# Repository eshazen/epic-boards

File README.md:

# epic-boards
Various small projects for EPIC and ENG classes

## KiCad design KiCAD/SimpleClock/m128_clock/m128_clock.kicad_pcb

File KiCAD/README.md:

Various small PCB projects for EPIC

    JumperBoards     - jumper boards for machine wiring
	me310-diff-amp   - instrumentation amp for ME310 class

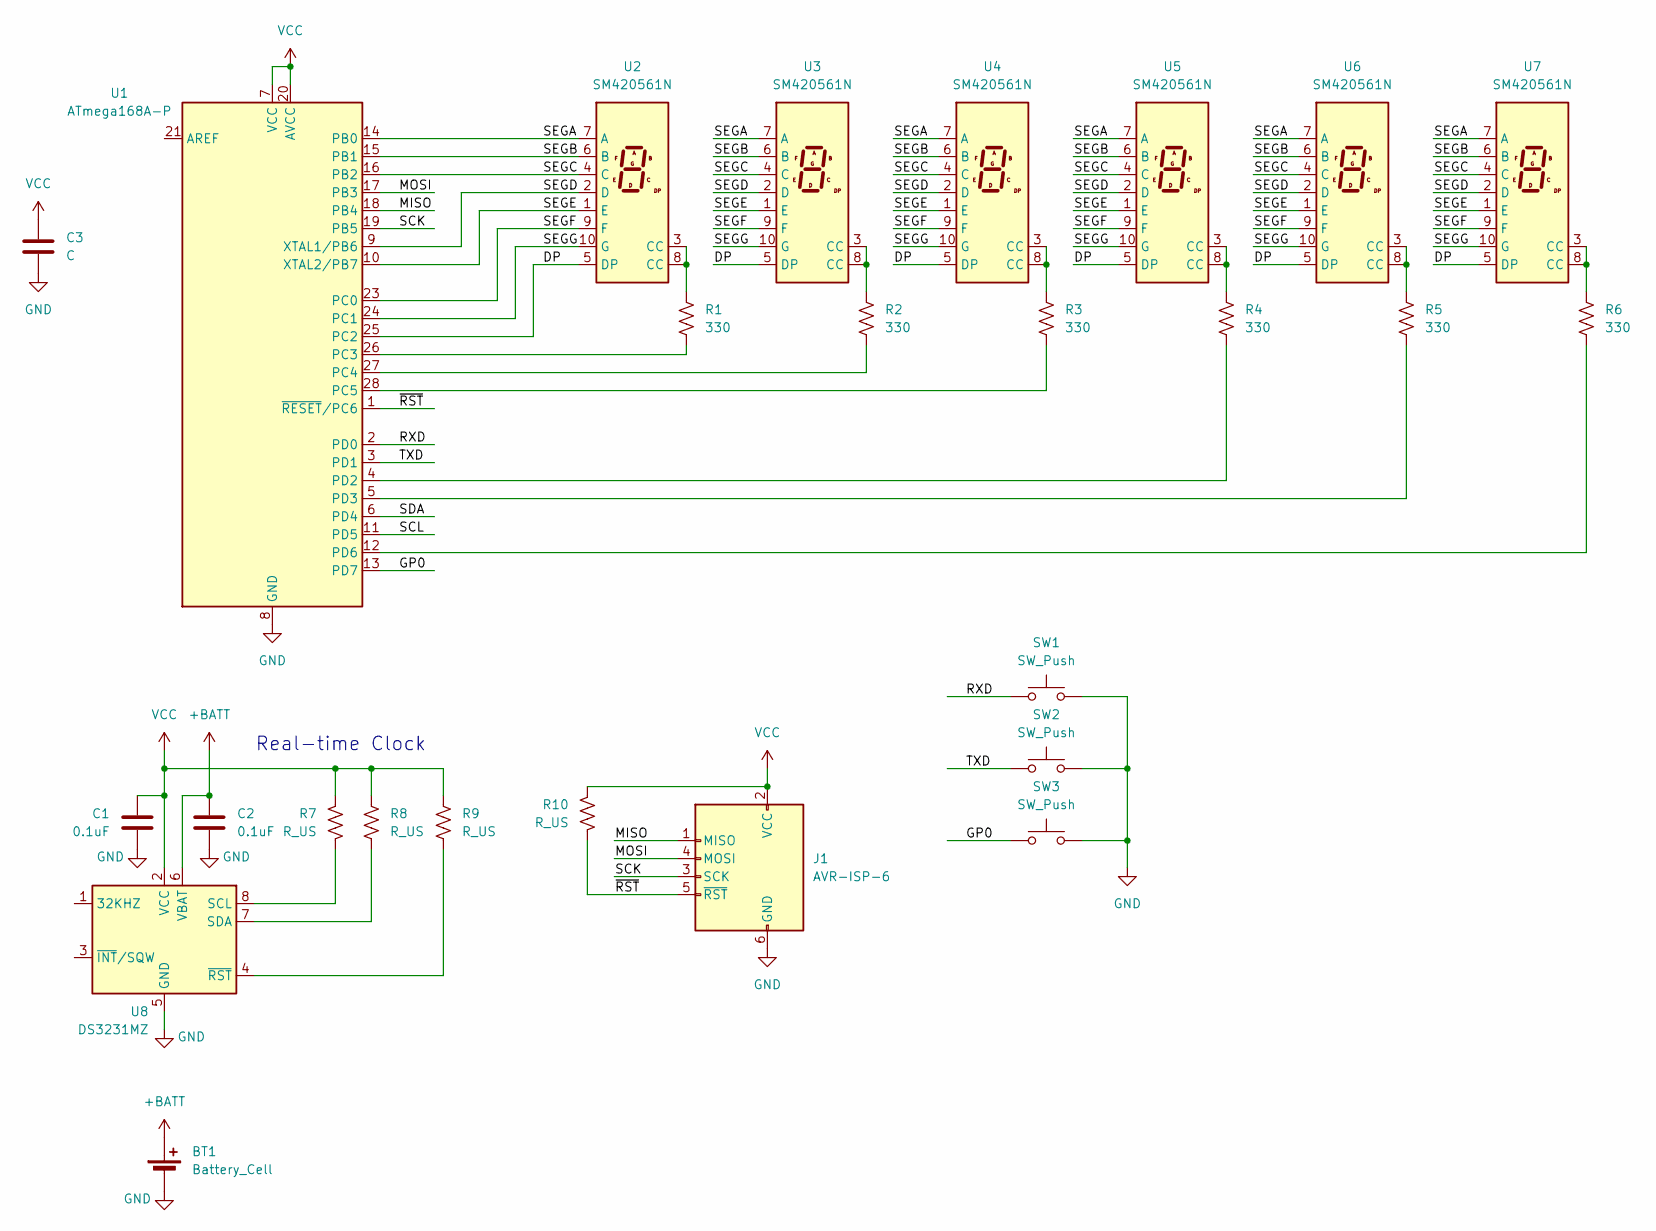
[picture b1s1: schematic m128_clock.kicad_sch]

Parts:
BT1: Battery_Cell; BatteryHolder_Keystone_103_1x20mm
C1, C2: 0.1uF; C_1206_3216Metric_Pad1.33x1.80mm_HandSolder
C3: C; C_Disc_D7.0mm_W2.5mm_P5.00mm
J1: AVR-ISP-6; PinHeader_2x03_P2.54mm_Vertical
R1, R2, R3, R4, R5, R6: 330; R_Axial_DIN0309_L9.0mm_D3.2mm_P12.70mm_Horizontal
R7, R8, R9, R10: R_US; R_1206_3216Metric
SW1, SW2, SW3: SW_Push; Push_SW
U1: ATmega168A-P; DIP-28_W7.62mm
U2, U3, U4, U5, U6, U7: SM420561N; 7SegmentLED_LTS6760_LTS6780
U8: DS3231MZ; SOIC-8_3.9x4.9mm_P1.27mm

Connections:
+BATT: BT1.1 (+), C2.1, U8.6 (VBAT)
/DP: U1.25 (PC2), U2.5 (DP), U3.5 (DP), U4.5 (DP), U5.5 (DP), U6.5 (DP), U7.5 (DP)
/GP0: SW3.1, U1.13 (PD7)
/MISO: J1.1 (MISO), U1.18 (PB4)
/MOSI: J1.4 (MOSI), U1.17 (PB3)
/RXD: SW1.1, U1.2 (PD0)
/SCK: J1.3 (SCK), U1.19 (PB5)
/SCL: U1.11 (PD5)
/SDA: U1.6 (PD4)
/SEGA: U1.14 (PB0), U2.7 (A), U3.7 (A), U4.7 (A), U5.7 (A), U6.7 (A), U7.7 (A)
/SEGB: U1.15 (PB1), U2.6 (B), U3.6 (B), U4.6 (B), U5.6 (B), U6.6 (B), U7.6 (B)
/SEGC: U1.16 (PB2), U2.4 (C), U3.4 (C), U4.4 (C), U5.4 (C), U6.4 (C), U7.4 (C)
/SEGD: U1.9 (XTAL1/PB6), U2.2 (D), U3.2 (D), U4.2 (D), U5.2 (D), U6.2 (D), U7.2 (D)
/SEGE: U1.10 (XTAL2/PB7), U2.1 (E), U3.1 (E), U4.1 (E), U5.1 (E), U6.1 (E), U7.1 (E)
/SEGF: U1.23 (PC0), U2.9 (F), U3.9 (F), U4.9 (F), U5.9 (F), U6.9 (F), U7.9 (F)
/SEGG: U1.24 (PC1), U2.10 (G), U3.10 (G), U4.10 (G), U5.10 (G), U6.10 (G), U7.10 (G)
/TXD: SW2.1, U1.3 (PD1)
/~RST: J1.5 (~RST), R10.2, U1.1 (~RESET/PC6)
GND: BT1.2 (-), C1.2, C2.2, C3.2, J1.6 (GND), SW1.2, SW2.2, SW3.2, U1.8 (GND), U1.22 (GND), U8.5 (GND)
unnamed: R1.1, U2.3 (CC), U2.8 (CC)
unnamed: R2.1, U3.3 (CC), U3.8 (CC)
unnamed: R3.1, U4.3 (CC), U4.8 (CC)
unnamed: R4.1, U5.3 (CC), U5.8 (CC)
unnamed: R5.1, U6.3 (CC), U6.8 (CC)
unnamed: R6.1, U7.3 (CC), U7.8 (CC)
unnamed: R1.2, U1.26 (PC3)
unnamed: R2.2, U1.27 (PC4)
unnamed: R3.2, U1.28 (PC5)
unnamed: R4.2, U1.4 (PD2)
unnamed: R5.2, U1.5 (PD3)
unnamed: R6.2, U1.12 (PD6)
unnamed: R7.2, U8.8 (SCL)
unnamed: R8.2, U8.7 (SDA)
unnamed: R9.2, U8.4 (~RST)
VCC: C1.1, C3.1, J1.2 (VCC), R7.1, R8.1, R9.1, R10.1, U1.7 (VCC), U1.20 (AVCC), U8.2 (VCC)

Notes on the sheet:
Real-time Clock

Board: 2 copper layers, 26 parts (0 on the bottom side), 33 nets, no tracks yet.

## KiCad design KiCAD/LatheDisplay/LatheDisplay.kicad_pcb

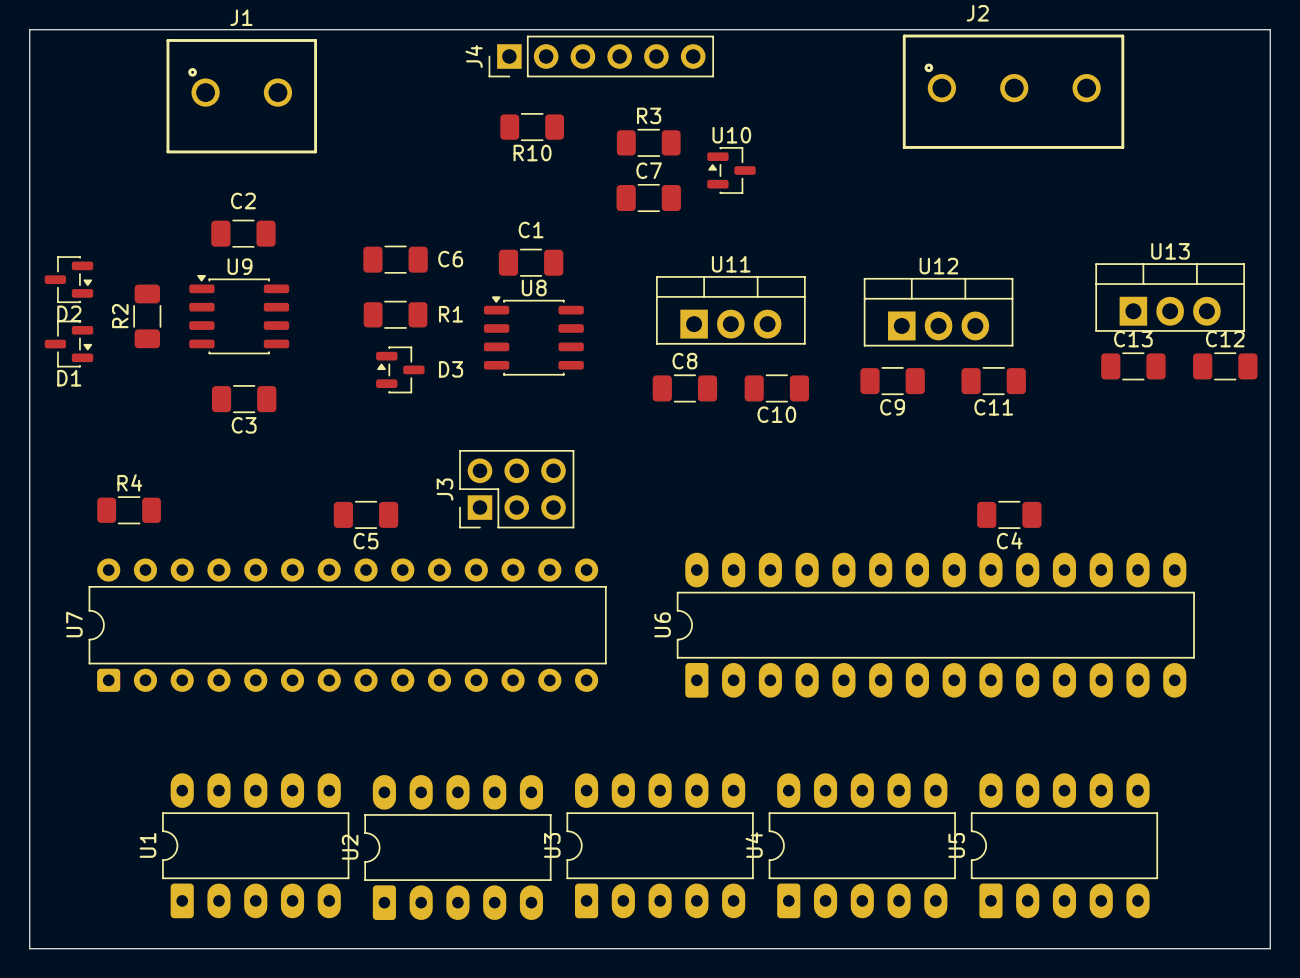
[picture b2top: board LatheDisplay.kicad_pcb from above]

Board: 2 copper layers, 85.7 x 63.5 mm, 38 parts (0 on the bottom side), 45 nets, no tracks yet.

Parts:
C1, C2, C3, C4, C5, C6, C7, C8, C9, C10, C11, C12, C13: 0.1uF; C_1206_3216Metric_Pad1.33x1.80mm_HandSolder
D1, D2, D3: BAV99; SOT-23
J1: Screw_Terminal_01x02; 691137710002
J2: Screw_Terminal_01x03; 3-pin-terminal
J3: AVR-ISP-6; PinHeader_2x03_P2.54mm_Vertical
J4: Conn_01x06_Pin; PinHeader_1x06_P2.54mm_Vertical
R1, R3, R4: 2k; R_1206_3216Metric_Pad1.30x1.75mm_HandSolder
R2: RGAIN; R_1206_3216Metric_Pad1.30x1.75mm_HandSolder
R10: 0R; R_1206_3216Metric_Pad1.30x1.75mm_HandSolder
U1, U2, U3, U4, U5: D168K; DIP-10_W7.62mm_LongPads
U6: ICM7218B; DIP-28_W7.62mm_LongPads
U7: ATmega328-P; DIP-28_W7.62mm
U8: TLC3541; SO-8_3.9x4.9mm_P1.27mm
U9: INA121; SO-8_3.9x4.9mm_P1.27mm
U10: LM4040DBZ-4.1; SOT-23
U11: LM7812_TO220; TO-220-3_Vertical
U12: LM7912_TO220; TO-220-3_Vertical
U13: LM7805_TO220; TO-220-3_Vertical

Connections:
+5V: C1.1, C4.1, C5.1, C12.1, D3.2 (A), J3.2 (VCC), R4.2, R10.1, U6.19 (V+), U7.7 (VCC), U7.20 (AVCC), U8.6 (VDD), U13.3 (VO)
+12V: C2.1, C10.1, D1.2 (A), D2.2 (A), R3.2, U9.8 (V+), U11.3 (VO)
+15V: C8.1, C13.1, J2.1, U11.1 (VI), U13.1 (VI)
-12V: C3.1, C11.1, D1.1 (K), D2.1 (K), U9.5 (V-), U12.3 (VO)
-15V: C9.1, J2.3, U12.2 (VI)
/ADC_CS: U7.6 (PD4), U8.1 (~CS)
/DP: U1.5 (DP), U2.5 (DP), U3.5 (DP), U4.5 (DP), U5.5 (DP), U6.4 (dp)
/FS: U7.5 (PD3), U8.7 (FS)
/MISO: J3.1 (MISO), U7.18 (PB4), U8.8 (SDO)
/MOSI: J3.4 (MOSI), U7.17 (PB3)
/RXD: J4.4, U7.2 (PD0)
/SA: U1.7 (A), U2.7 (A), U3.7 (A), U4.7 (A), U5.7 (A), U6.27 (a)
/SB: U1.6 (B), U2.6 (B), U3.6 (B), U4.6 (B), U5.6 (B), U6.3 (b)
/SC: U1.4 (C), U2.4 (C), U3.4 (C), U4.4 (C), U5.4 (C), U6.1 (c)
/SCK: J3.3 (SCK), U7.19 (PB5), U8.5 (SCLK)
/SD: U1.2 (D), U2.2 (D), U3.2 (D), U4.2 (D), U5.2 (D), U6.25 (d)
/SE: U1.1 (E), U2.1 (E), U3.1 (E), U4.1 (E), U5.1 (E), U6.2 (e)
/SF: U1.9 (F), U2.9 (F), U3.9 (F), U4.9 (F), U5.9 (F), U6.24 (f)
/SG: U1.10 (G), U2.10 (G), U3.10 (G), U4.10 (G), U5.10 (G), U6.26 (g)
/TXD: J4.5, U7.3 (PD1)
/~RESET: J3.5 (~RST), R4.1, U7.1 (~RESET/PC6)
GND: C1.2, C2.2, C3.2, C4.2, C5.2, C6.2, C7.2, C8.2, C9.2, C10.2, C11.2, C12.2, C13.2, D3.1 (K), J2.2, J3.6 (GND), J4.1, U6.28 (GND), U7.8 (GND), U7.22 (GND), U8.3 (GND), U9.6 (Ref), U10.2 (A), U11.2 (GND), U12.1 (GND), U13.2 (GND)
unnamed: D1.3 (K), J1.1, U9.4 (+)
unnamed: D2.3 (K), J1.2, U9.1 (-)
unnamed: J4.3, R10.2
unnamed: R1.1, U9.7
unnamed: R2.1, U9.3 (Rg)
unnamed: R2.2, U9.2 (Rg)
unnamed: U6.12 (ID0), U7.14 (PB0)
unnamed: U6.11 (ID1), U7.15 (PB1)
unnamed: U6.13 (ID2), U7.16 (PB2)
unnamed: U6.14 (ID3), U7.9 (XTAL1/PB6)
unnamed: U6.10 (ID4), U7.10 (XTAL2/PB7)
unnamed: U6.6 (ID5), U7.23 (PC0)
unnamed: U6.5 (ID6), U7.24 (PC1)
unnamed: U6.7 (ID7), U7.25 (PC2)
unnamed: U6.9 (MODE), U7.4 (PD2)
unnamed: U1.3 (CC), U1.8 (CC), U6.15 (d1)
unnamed: U2.3 (CC), U2.8 (CC), U6.16 (d2)
unnamed: U3.3 (CC), U3.8 (CC), U6.23 (d3)
unnamed: U4.3 (CC), U4.8 (CC), U6.20 (d4)
unnamed: U5.3 (CC), U5.8 (CC), U6.17 (d5)
unnamed: U6.8 (nWR), U7.26 (PC3)
unnamed: C6.1, D3.3 (K), R1.2, U8.4 (AIN)
unnamed: C7.1, R3.1, U8.2 (REF), U10.1 (K)

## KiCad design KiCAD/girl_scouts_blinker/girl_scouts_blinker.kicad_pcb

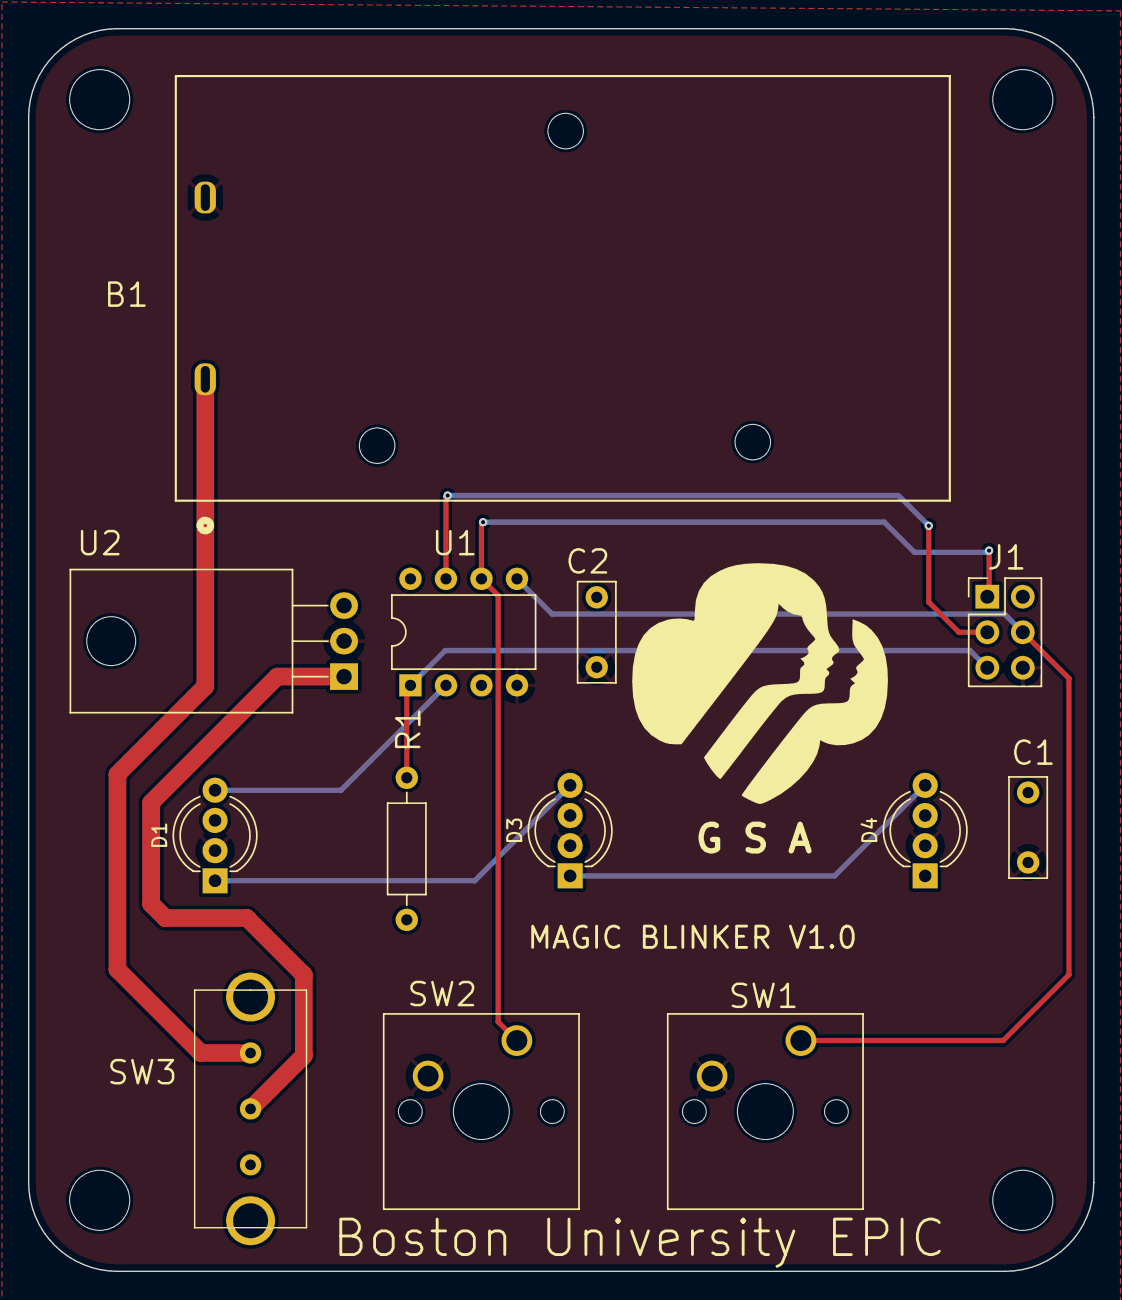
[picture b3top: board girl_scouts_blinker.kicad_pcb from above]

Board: 2 copper layers, 76.2 x 88.9 mm, 18 parts (0 on the bottom side), 11 nets.

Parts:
B1: BC9VPC; BC9VPC_MPD
C1, C2: 0.1uF; C_Disc_D7.0mm_W2.5mm_P5.00mm
D1, D3, D4: Adafruit NeoPixel_THT; LED_D5.0mm-4_RGB_Wide_Pins
FID1: Fiducial; gs_logo
H1, H2, H3, H4: MountingHole; MountingHole_4.3mm_M4
J1: AVR-ISP-6; PinHeader_2x03_P2.54mm_Vertical
R1: 10k; R_Axial_DIN0207_L6.3mm_D2.5mm_P10.16mm_Horizontal
SW1, SW2: SW_Push; SW_Cherry_MX_1.00u_PCB
SW3: SW_SPST; Slide_SLW-1711575-5A-N-D
U1: ATtiny85-20P; DIP-8_W7.62mm
U2: LM7805_TO220; TO-220-3_Horizontal_TabDown

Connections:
+5V: C1.1, C2.1, D1.3 (VDD), D3.3 (VDD), D4.3 (VDD), J1.2 (VCC), R1.1, U1.8 (VCC), U2.3 (VO)
+6V: B1.1, SW3.1 (A)
/MISO: J1.1 (MISO), SW2.1, U1.6 (PB1)
/MOSI: J1.4 (MOSI), SW1.1, U1.5 (AREF/PB0)
/SCK: J1.3 (SCK), U1.7 (PB2)
/nRST: J1.5 (~RST), R1.2, U1.1 (~RESET/PB5)
GND: B1.2, C1.2, C2.2, D1.2 (GND), D3.2 (GND), D4.2 (GND), J1.6 (GND), SW1.2, SW2.2, U1.4 (GND), U2.2 (GND)
unnamed: D1.4 (DIN), U1.2 (XTAL1/PB3)
unnamed: D1.1 (DOUT), D3.4 (DIN)
unnamed: D3.1 (DOUT), D4.4 (DIN)
unnamed: SW3.2 (B), U2.1 (VI)

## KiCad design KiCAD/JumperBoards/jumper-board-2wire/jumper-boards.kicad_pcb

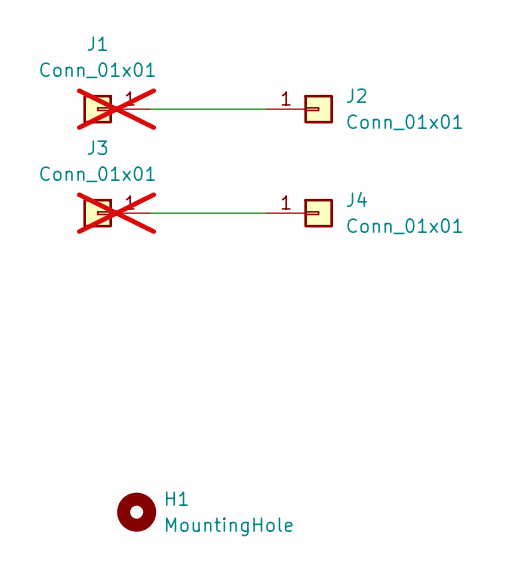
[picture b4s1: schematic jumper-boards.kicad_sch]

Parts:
H1: MountingHole; hole-440-nopad
J1, J3: Conn_01x01; PinHeader_1x01_P2.54mm_Vertical; not fitted
J2, J4: Conn_01x01; PinHeader_1x01_P2.54mm_Vertical

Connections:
unnamed: J1.1, J2.1
unnamed: J3.1, J4.1

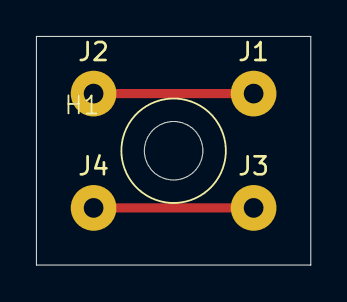
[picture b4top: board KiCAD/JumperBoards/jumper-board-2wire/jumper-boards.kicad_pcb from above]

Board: 2 copper layers, 15.2 x 12.7 mm, 5 parts (0 on the bottom side), 2 nets.

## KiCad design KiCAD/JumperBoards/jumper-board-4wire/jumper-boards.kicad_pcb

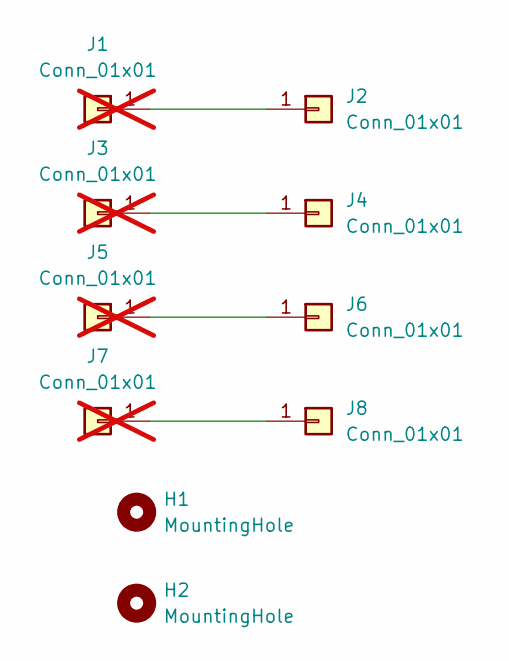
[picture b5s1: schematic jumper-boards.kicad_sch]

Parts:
H1, H2: MountingHole; hole-440-nopad
J1, J3, J5, J7: Conn_01x01; PinHeader_1x01_P2.54mm_Vertical; not fitted
J2, J4, J6, J8: Conn_01x01; PinHeader_1x01_P2.54mm_Vertical

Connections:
unnamed: J1.1, J2.1
unnamed: J3.1, J4.1
unnamed: J5.1, J6.1
unnamed: J7.1, J8.1

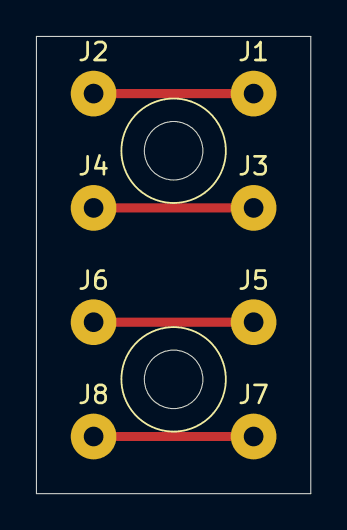
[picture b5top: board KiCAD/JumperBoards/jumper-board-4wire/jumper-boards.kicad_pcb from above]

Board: 2 copper layers, 15.2 x 25.4 mm, 10 parts (0 on the bottom side), 4 nets.

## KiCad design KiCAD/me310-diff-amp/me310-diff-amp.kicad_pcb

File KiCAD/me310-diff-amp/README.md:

# me310-diff-amp

This is a clone of an existing design with a differential amplifier
based on the classic 741 op-amp.  It has +/- signal inputs, a
single-ended output, and power supply connections.

Power supplies can be up to +/-15V per the specs of the 741.

With both + and - inputs connected, the differential voltage gain is
100.0.  If the "Sig+" input is unused, it must be grounded, else the
gain drops to 10.

There is no compensation or offset null in this circuit, so DC offsets
are large and there is dramatic ringing with high frequency inputs.

# Rev 2.0 board

There is one error on this version... the Sig+ input is not connected.
The easiest fix is to extend the lead of R1 to solder to the Sig+
input.

This version was fabricated and delivered on 3/4/24 (qty 25).

# Rev 2.1 board

This revision has the above error corrected.  As of this writing
(3/18/24) this version has not been fabricated.

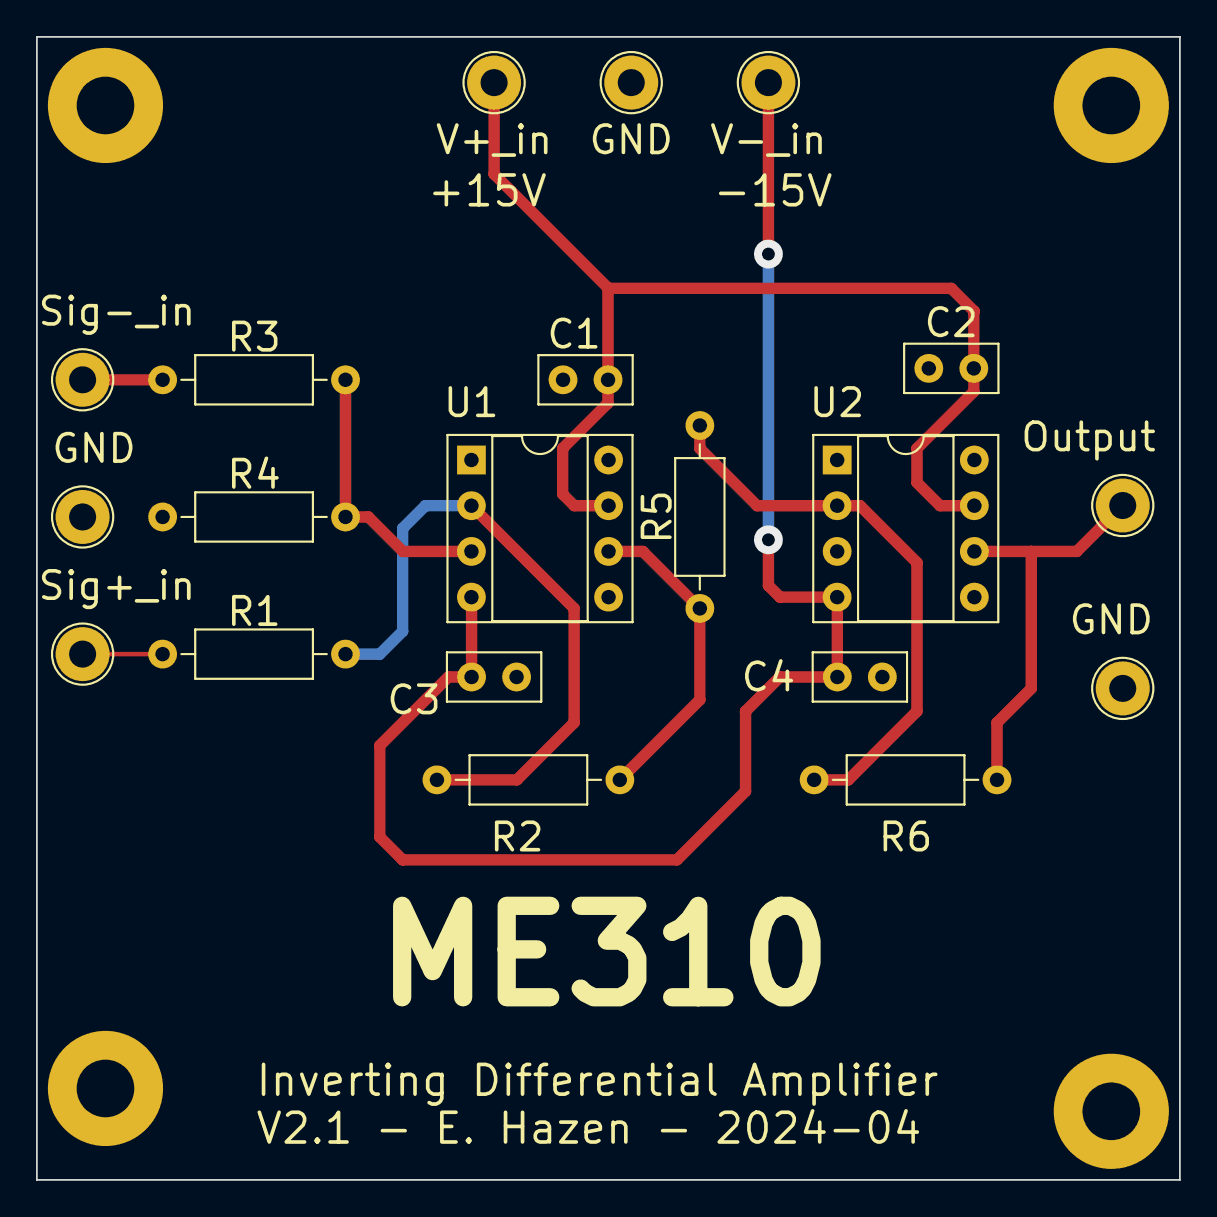
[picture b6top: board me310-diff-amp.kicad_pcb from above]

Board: 2 copper layers, 63.5 x 63.5 mm, 24 parts (0 on the bottom side), 10 nets.

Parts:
C1, C2, C3, C4: C; C_Disc_D5.0mm_W2.5mm_P2.50mm
H1, H2, H3, H4: MountingHole; MountingHole_3.2mm_M3_Pad
R1, R2, R3, R4, R5, R6: R_US; R_Axial_DIN0207_L6.3mm_D2.5mm_P10.16mm_Horizontal
TP1: V+_in; TestPoint_Loop_D2.54mm_Drill1.5mm_Beaded
TP2: V-_in; TestPoint_Loop_D2.54mm_Drill1.5mm_Beaded
TP3, TP6, TP8: GND; TestPoint_Loop_D2.54mm_Drill1.5mm_Beaded
TP4: Sig-_in; TestPoint_Loop_D2.54mm_Drill1.5mm_Beaded
TP5: Sig+_in; TestPoint_Loop_D2.54mm_Drill1.5mm_Beaded
TP7: Output; TestPoint_Loop_D2.54mm_Drill1.5mm_Beaded
U1, U2: LM741; DIP-8_W7.62mm_Socket

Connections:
+15V: C1.1, C2.1, TP1.1, U1.7 (V+), U2.7 (V+)
-15V: C3.1, C4.1, TP2.1, U1.4 (V-), U2.4 (V-)
GND: C1.2, C2.2, C3.2, C4.2, R4.1, TP3.1, TP6.1, TP8.1, U2.3 (+)
unnamed: R1.1, TP5.1
unnamed: R2.2, R5.1, U1.6
unnamed: R3.1, TP4.1
unnamed: R6.1, TP7.1, U2.6
unnamed: R3.2, R4.2, U1.3 (+)
unnamed: R1.2, R2.1, U1.2 (-)
unnamed: R5.2, R6.2, U2.2 (-)

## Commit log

2024-02-12 schem
2024-02-12 Rev 2.0 ready?
2024-03-05 as built V1
2024-03-18 Rev 2.1 changes, README
2024-10-22 start on jumper boards, add README
2024-10-30 jumper boards, start GSA board
2024-11-09 add programming connector and RST R
2024-11-12 layout v1.1 done?
2024-11-12 ready to order?
2024-11-13 updated PCB
2024-11-28 starting GS software on T85
2024-11-28 ws2812 demo
2024-11-28 readme, working RGB blinky
2024-11-30 RGB rainbow table utility
2024-11-30 add rainbow effect
2024-12-03 software works on real hardware!
2024-12-07 software
2024-12-16 working rainbow on PCB
2024-12-16 add wake-up demo
2025-01-26 working on candidate final firmware
2025-02-02 working on firmware for GSA
2025-02-02 Release Rev 1.0 software
2025-02-06 soldering jig
2025-11-26 components assigned and tentative placement
2026-01-27 save lathe stuff
2026-02-19 start on clock
